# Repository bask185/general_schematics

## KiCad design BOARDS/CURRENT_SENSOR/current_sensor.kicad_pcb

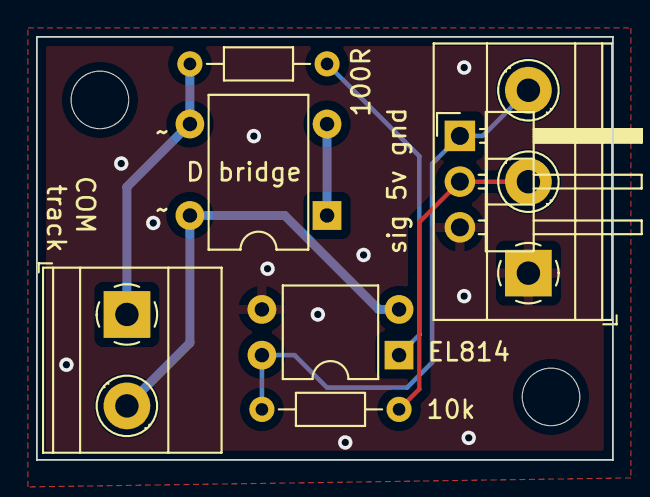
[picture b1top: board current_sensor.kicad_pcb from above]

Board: 2 copper layers, 32.0 x 23.5 mm, 7 parts (0 on the bottom side), 7 nets.

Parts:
D1201: D; Diode_Bridge_DIP-4_W7.62mm_P5.08mm
J1201: tracks; TerminalBlock_Phoenix_MKDS-1,5-2-5.08_1x02_P5.08mm_Horizont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
J1202: ter; TerminalBlock_Phoenix_MKDS-1,5-3-5.08_1x03_P5.08mm_Horizont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
J1203: ter; PinHeader_1x03_P2.54mm_Horizontal
R1201: 100R; R_Axial_DIN0204_L3.6mm_D1.6mm_P7.62mm_Horizontal
R1202: 10k; R_Axial_DIN0204_L3.6mm_D1.6mm_P7.62mm_Horizontal
U1201: EL814; DIP-4_W7.62mm

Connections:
+5V: J1202.2, J1203.2, R1202.1
GND: J1202.1, J1203.3, U1201.3
unnamed: D1201.1 (+), D1201.2 (-)
unnamed: D1201.3, J1201.1, R1201.1
unnamed: D1201.4, J1201.2, U1201.2
unnamed: R1201.2, U1201.1
sig: J1202.3, J1203.1, R1202.2, U1201.4

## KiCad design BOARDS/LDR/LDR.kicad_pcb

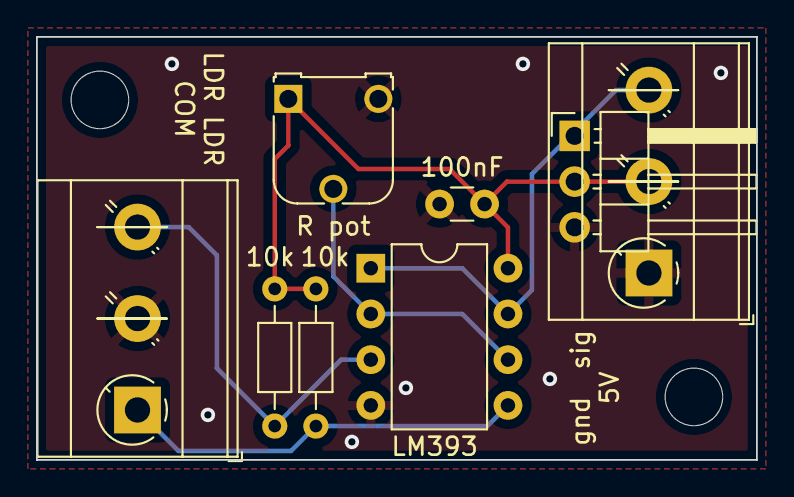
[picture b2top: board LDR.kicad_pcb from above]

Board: 2 copper layers, 40.0 x 23.5 mm, 8 parts (0 on the bottom side), 6 nets.

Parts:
C: 100nF; C_Disc_D3.0mm_W1.6mm_P2.50mm
J1101: LDR; TerminalBlock_MetzConnect_Type073_RT02603HBLU_1x03_P5.08mm_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
J1102: ter; PinHeader_1x03_P2.54mm_Horizontal
J1103: ter; TerminalBlock_MetzConnect_Type073_RT02603HBLU_1x03_P5.08mm_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
R1101, R1102: 10k; R_Axial_DIN0204_L3.6mm_D1.6mm_P7.62mm_Horizontal
R pot: REF; Potentiometer_Runtron_RM-065_Vertical
U1101: LM393; DIP-8_W7.62mm

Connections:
+5V: C.1, J1102.2, J1103.2, R1101.1, R1102.1, R pot.1, U1101.8 (V+)
GND: C.2, J1101.2, J1102.3, J1103.1, R pot.3, U1101.4 (V-)
unnamed: J1101.1, R1101.2, U1101.5 (+)
unnamed: J1101.3, R1102.2, U1101.3 (+)
unnamed: J1102.1, J1103.3, U1101.1, U1101.7
unnamed: R pot.2, U1101.2 (-), U1101.6 (-)

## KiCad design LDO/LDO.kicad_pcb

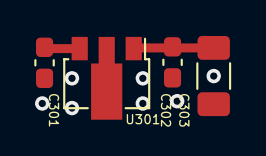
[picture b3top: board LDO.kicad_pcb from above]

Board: 2 copper layers, 4 parts (0 on the bottom side), 3 nets.

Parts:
C301: 330nF; C_0603_1608Metric_Pad1.08x0.95mm_HandSolder
C302: 100nF; C_0603_1608Metric_Pad1.08x0.95mm_HandSolder
C303: 100uF; C_1206_3216Metric_Pad1.33x1.80mm_HandSolder
U301: L78L05_SOT89; SOT-89-3

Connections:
/5V: C302.1, C303.1, U301.1 (OUT)
/GND: C301.2, C302.2, C303.2, U301.2 (GND)
/Vin: C301.1, U301.3 (IN)

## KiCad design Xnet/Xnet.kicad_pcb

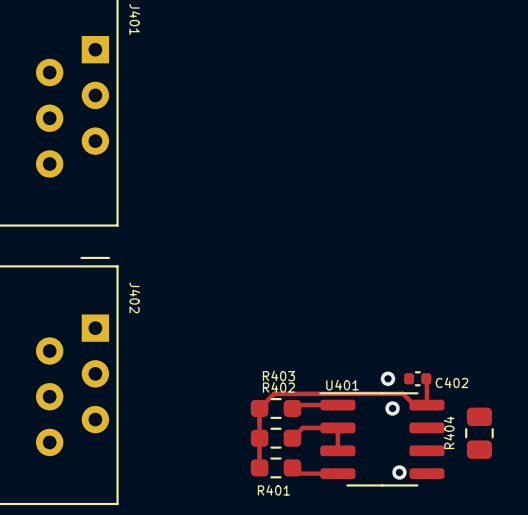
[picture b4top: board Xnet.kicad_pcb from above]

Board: 2 copper layers, 8 parts (0 on the bottom side), 8 nets.

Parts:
C402: 100nF; C_0402_1005Metric
J401, J402: RJ12
R401, R402, R403: 10k; R_0603_smalltext
R404: 120R; R_0805_2012Metric
U401: MAX485E; SOIC-8_3.9x4.9mm_P1.27mm

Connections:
/5V: C402.1, R401.1, R402.1, R403.1, U401.8 (VCC)
/12V: J401.5, J402.5
/A: J401.4, J402.4, R404.1, U401.6 (A)
/B: J401.3, J402.3, R404.2, U401.7 (B)
/GND: C402.2, J401.2, J402.2, U401.5 (GND)
/RS485_DIR: R402.2, U401.2 (~RE), U401.3 (DE)
/Rx: R403.2, U401.1 (RO)
/Tx: R401.2, U401.4 (DI)
